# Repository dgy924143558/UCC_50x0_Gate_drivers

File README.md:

## Upcoming Updates

I will be updating this documentation with the latest information and instructions in the near future. 

## Application

This design is specifically tailored for use in power switching applications and is compatible with various types of switches including:

- **IGBT (Insulated Gate Bipolar Transistor)**: Ideal for high-voltage, high-current applications.
- **MOSFET (Metal-Oxide-Semiconductor Field-Effect Transistor)**: Suitable for fast switching with lower power loss.
- **SiCFET (Silicon Carbide Field-Effect Transistor)**: Perfect for high-efficiency, high-frequency operations.

## References

This design was informed by the following sources:

- [UCC5350]([URL of Reference 1](https://www.ti.com/lit/ds/symlink/ucc5350.pdf?ts=1702973246752&ref_url=https%253A%252F%252Fwww.ti.com%252Fproduct%252Fja-jp%252FUCC5350%253FkeyMatch%253DUCC5350%2526tisearch%253Dsearch-everything%2526usecase%253DGPN-ALT))
- [evstgap2sicsn]([URL of Reference 2](https://www.st.com/resource/en/data_brief/evstgap2sicsn.pdf))

I am grateful to these resources for providing valuable information and inspiration for this project.

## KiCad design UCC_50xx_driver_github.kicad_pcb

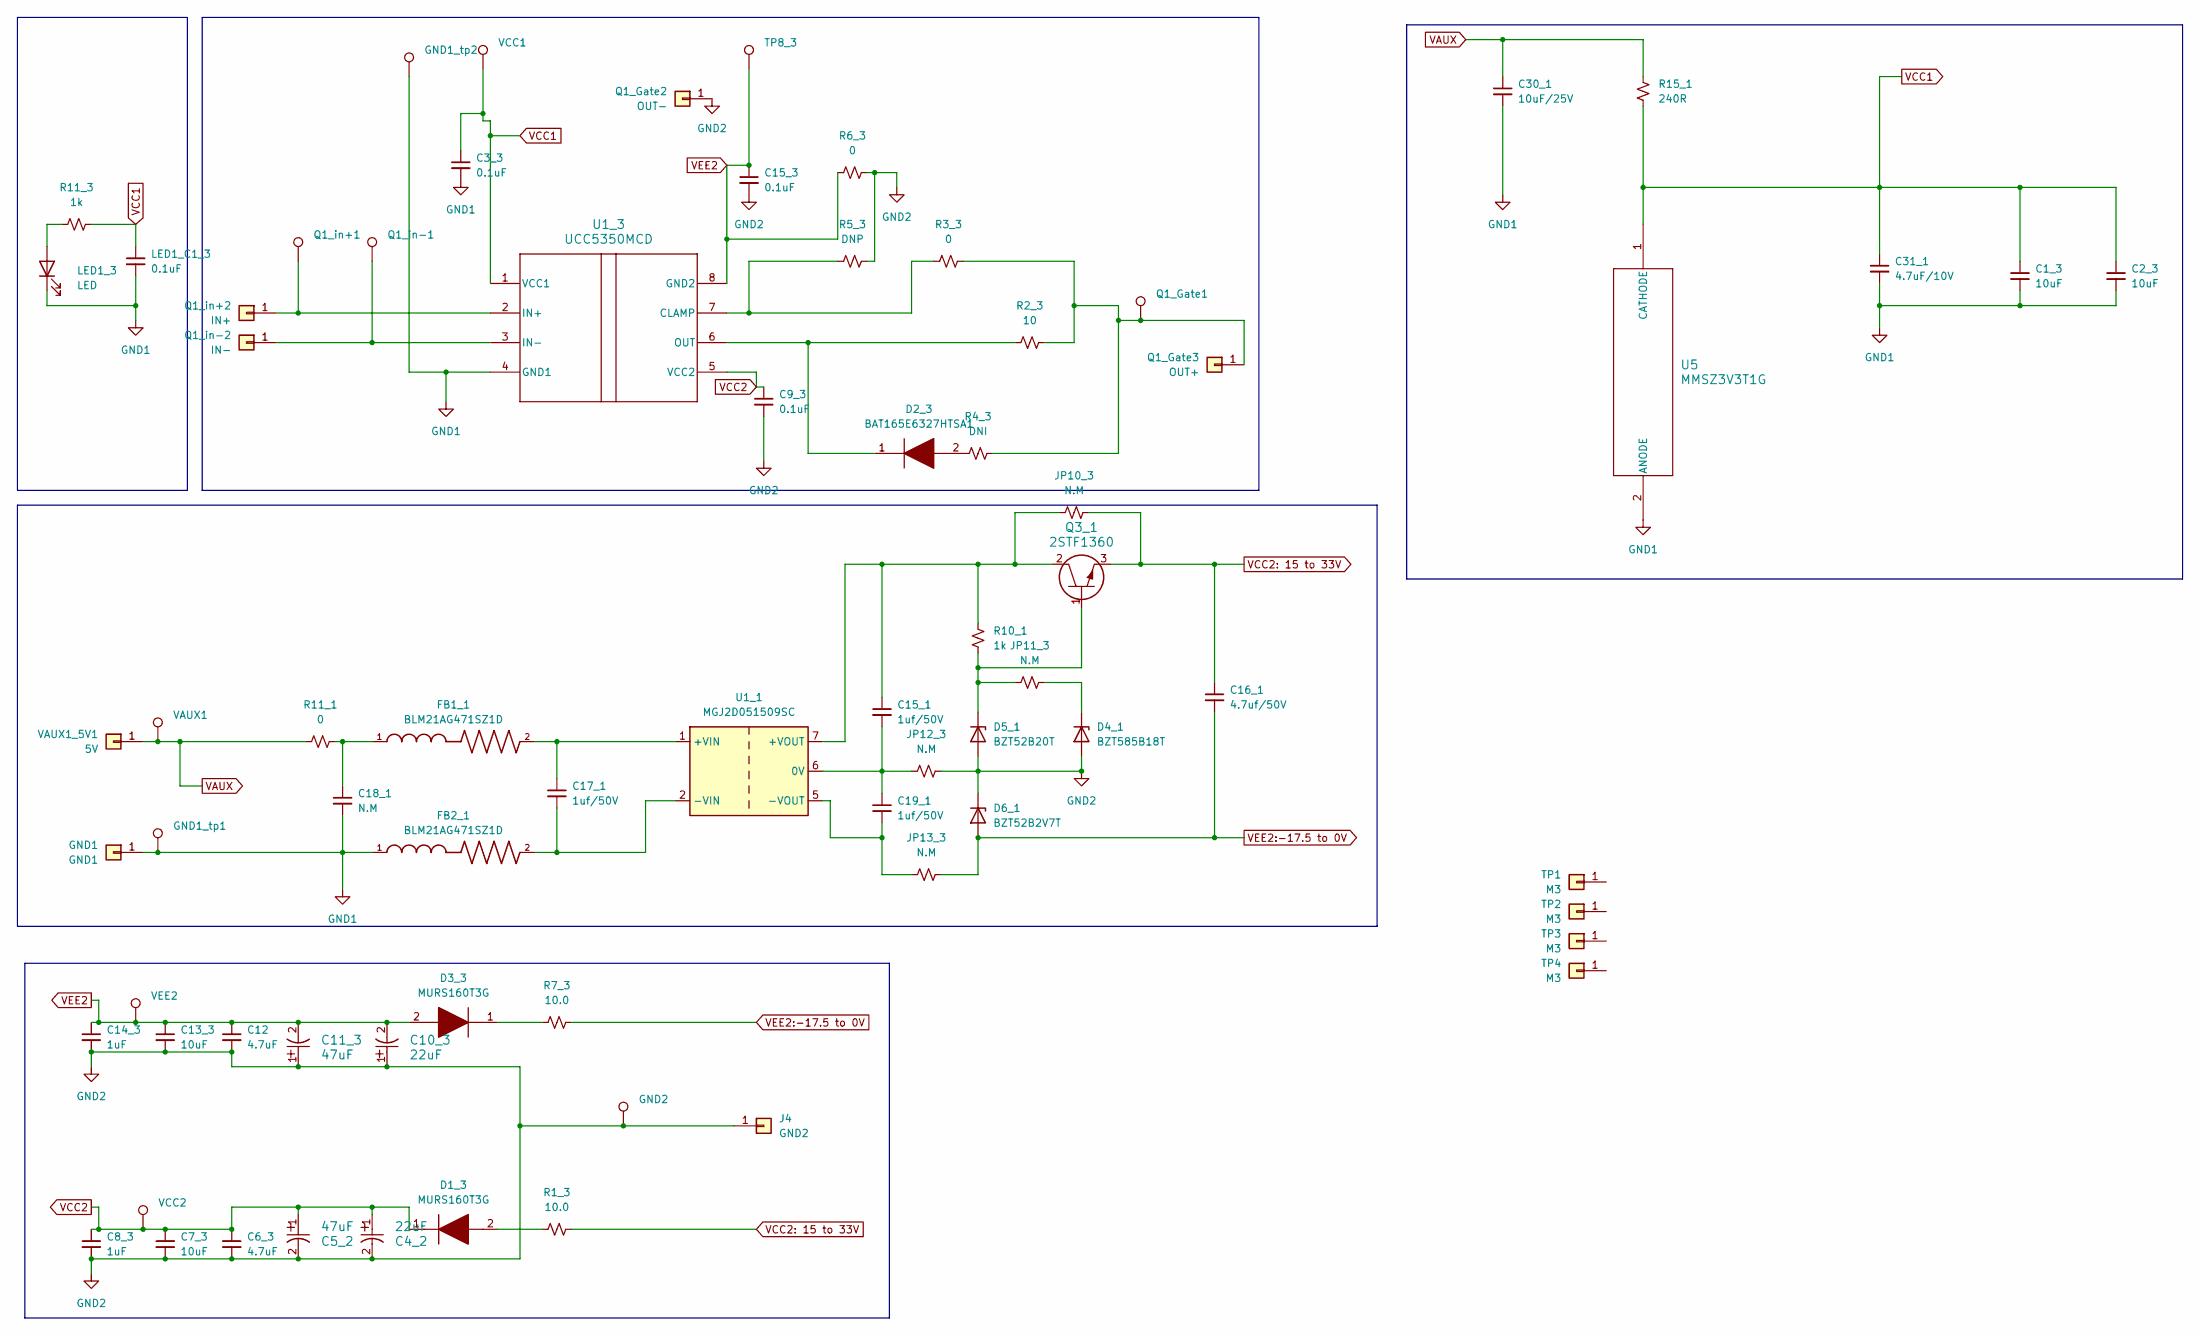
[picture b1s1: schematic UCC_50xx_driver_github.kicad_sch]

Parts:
C1_3, C2_3: 10uF; C_0805_2012Metric
C3_3, C9_3, C15_3: 0.1uF; C_0805_2012Metric
C4_2, C10_3: 22uF; CAP_6.3 X 5.8_PAN-M
C5_2, C11_3: 47uF; CAP_EEFK_D8_PAN-M
C6_3, C12: 4.7uF; C_0805_2012Metric
C7_3, C13_3: 10uF; C_1206_3216Metric
C8_3, C14_3: 1uF; C_0805_2012Metric
C15_1, C17_1, C19_1: 1uf/50V; R_0805_2012Metric
C16_1: 4.7uf/50V; R_1206_3216Metric
C18_1: N.M; C_0805_2012Metric
C30_1: 10uF/25V; C_0805_2012Metric
C31_1: 4.7uF/10V; C_0805_2012Metric
D1_3, D3_3: MURS160T3G; SOD2513X110N; Mouser Part Number 726-BAT165E6327HTSA1
D2_3: BAT165E6327HTSA1; SOD2513X110N; Mouser Part Number 726-BAT165E6327HTSA1
D4_1: BZT585B18T; D_SOD-523
D5_1: BZT52B20T; D_SOD-523
D6_1: BZT52B2V7T; D_SOD-523
FB1_1, FB2_1: BLM21AG471SZ1D; BEADC2012X105N
GND1: GND1; SolderWirePad_single_SMD_5x10mm
GND1_tp1, GND1_tp2, GND2: TestPoint; TestPoint_Keystone_5019_Minature
J4: GND2; SolderWirePad_single_SMD_5x10mm
JP10_3, JP11_3, JP12_3, JP13_3: N.M; R_1206_3216Metric
LED1_3: LED; C_0805_2012Metric
LED1_C1_3: 0.1uF; C_0805_2012Metric
Q1_Gate1, Q1_in+1, Q1_in-1: TestPoint; TestPoint_Keystone_5019_Minature
Q1_Gate2: OUT-; SolderWirePad_single_SMD_5x10mm
Q1_Gate3: OUT+; SolderWirePad_single_SMD_5x10mm
Q1_in+2: IN+; SolderWirePad_single_SMD_5x10mm
Q1_in-2: IN-; SolderWirePad_single_SMD_5x10mm
Q3_1: 2STF1360; SOT-89_STM
R1_3, R7_3: 10.0; R_1210_3225Metric
R2_3: 10; R_1210_3225Metric
R3_3, R6_3: 0; R_1210_3225Metric
R4_3: DNI; R_1210_3225Metric
R5_3: DNP; C_0805_2012Metric
R10_1: 1k; R_0805_2012Metric
R11_1: 0; R_0805_2012Metric
R11_3: 1k; C_0805_2012Metric
R15_1: 240R; C_0805_2012Metric
TP1, TP2, TP3, TP4: M3; MountingHole_3.2mm_M3_Pad
TP8_3: TestPoint; TestPoint_Keystone_5019_Minature
U1_1: MGJ2D051509SC; Converter_DCDC_Murata_MGJ2DxxxxxxSC_THT
U1_3: UCC5350MCD; D0008B_M
U5: MMSZ3V3T1G; SOD-123_ONS-M
VAUX1: TestPoint; TestPoint_Keystone_5019_Minature
VAUX1_5V1: 5V; SolderWirePad_single_SMD_5x10mm
VCC1, VCC2: TestPoint; TestPoint_Keystone_5019_Minature
VEE2: TestPoint; TestPoint_Keystone_5019_Minature

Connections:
GND1: C1_3.2, C2_3.2, C3_3.2, C18_1.2, C30_1.2, C31_1.2, FB2_1.1, GND1.1, GND1_tp1.1, GND1_tp2.1, LED1_3.1 (K), LED1_C1_3.2, U1_3.4 (GND1), U5.2 (ANODE)
GND2: C4_2.2, C5_2.2, C6_3.2, C7_3.2, C8_3.2, C9_3.2, C10_3.1, C11_3.1, C12.2, C13_3.2, C14_3.2, C15_3.2, D4_1.2 (A), D5_1.2 (A), D6_1.1 (K), GND2.1, J4.1, JP12_3.2, Q1_Gate2.1, R5_3.2, R6_3.2
unnamed: C18_1.1, FB1_1.1, R11_1.2
unnamed: D1_3.2, R1_3.1
unnamed: D2_3.2, R4_3.1
unnamed: D3_3.1, R7_3.1
unnamed: D4_1.1 (K), JP11_3.2
unnamed: D5_1.1 (K), JP11_3.1, Q3_1.1, R10_1.2
unnamed: LED1_3.2 (A), R11_3.1
unnamed: Q1_Gate1.1, Q1_Gate3.1, R2_3.2, R3_3.2, R4_3.2
unnamed: Q1_in+1.1, Q1_in+2.1, U1_3.2 (IN+)
unnamed: Q1_in-1.1, Q1_in-2.1, U1_3.3 (IN-)
unnamed: C15_1.2, C19_1.1, JP12_3.1, U1_1.6 (0V)
unnamed: C17_1.1, FB1_1.2, U1_1.1 (+VIN)
unnamed: C15_1.1, JP10_3.1, Q3_1.2, R10_1.1, U1_1.7 (+VOUT)
unnamed: C17_1.2, FB2_1.2, U1_1.2 (-VIN)
unnamed: C19_1.2, JP13_3.1, U1_1.5 (-VOUT)
unnamed: R3_3.1, R5_3.1, U1_3.7 (CLAMP)
unnamed: D2_3.1, R2_3.1, U1_3.6 (OUT)
VAUX: C30_1.1, R11_1.1, R15_1.1, VAUX1.1, VAUX1_5V1.1
VCC1: C1_3.1, C2_3.1, C3_3.1, C31_1.1, LED1_C1_3.1, R11_3.2, R15_1.2, U1_3.1 (VCC1), U5.1 (CATHODE), VCC1.1
VCC2: C4_2.1, C5_2.1, C6_3.1, C7_3.1, C8_3.1, C9_3.1, D1_3.1, U1_3.5 (VCC2), VCC2.1
VCC2: 15 to 33V: C16_1.1, JP10_3.2, Q3_1.3, R1_3.2
VEE2: C10_3.2, C11_3.2, C12.1, C13_3.1, C14_3.1, C15_3.1, D3_3.2, R6_3.1, TP8_3.1, U1_3.8 (GND2), VEE2.1
VEE2:-17.5 to 0V: C16_1.2, D6_1.2 (A), JP13_3.2, R7_3.2

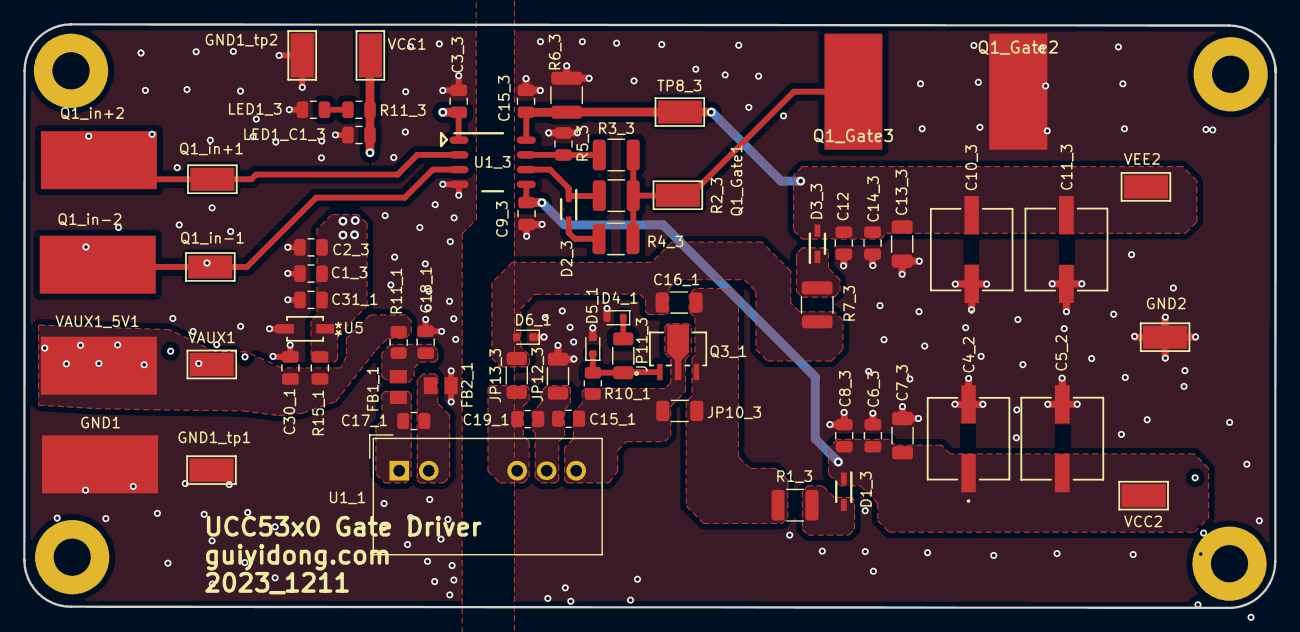
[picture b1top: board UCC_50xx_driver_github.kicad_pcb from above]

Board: 4 copper layers, 107.8 x 50.3 mm, 72 parts (0 on the bottom side), 25 nets.

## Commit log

2023-12-19 README.md
2023-12-19 Rename タイトルなし - 副本.png to タイトルなし2.png
